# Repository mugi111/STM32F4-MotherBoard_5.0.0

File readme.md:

### 概要
1. STM32F4-MotherBoard_5.0.0  
STM32F407VGのマザーボード  
回路図，実体配線図
KiCADプロジェクト

2. RCsemiSTM32F4_Ver400
STM32F4MBライブラリ  
使用ライブラリ:SPD(Standard Peripheral Driver)  
使用言語:C

3. RCsemiSTM32F4_Ver500
STM32F4MBライブラリ  
使用ライブラリ:HAL Driver  
使用言語:C++

|STM32F4MB500|個数||
|---------|-----|-------------|
|ADC      |1    |BOXHEADER    |
|CAN      |2    |RJ45         |
|RS232C   |2    |RJ12         |
|DisitalIO|2    |BOXHEADER    |
|PushSW   |1    |DTS-6        |
|RotarySW |1    |             |
|LED      |1    |             |
|MicroSD  |1    |             |

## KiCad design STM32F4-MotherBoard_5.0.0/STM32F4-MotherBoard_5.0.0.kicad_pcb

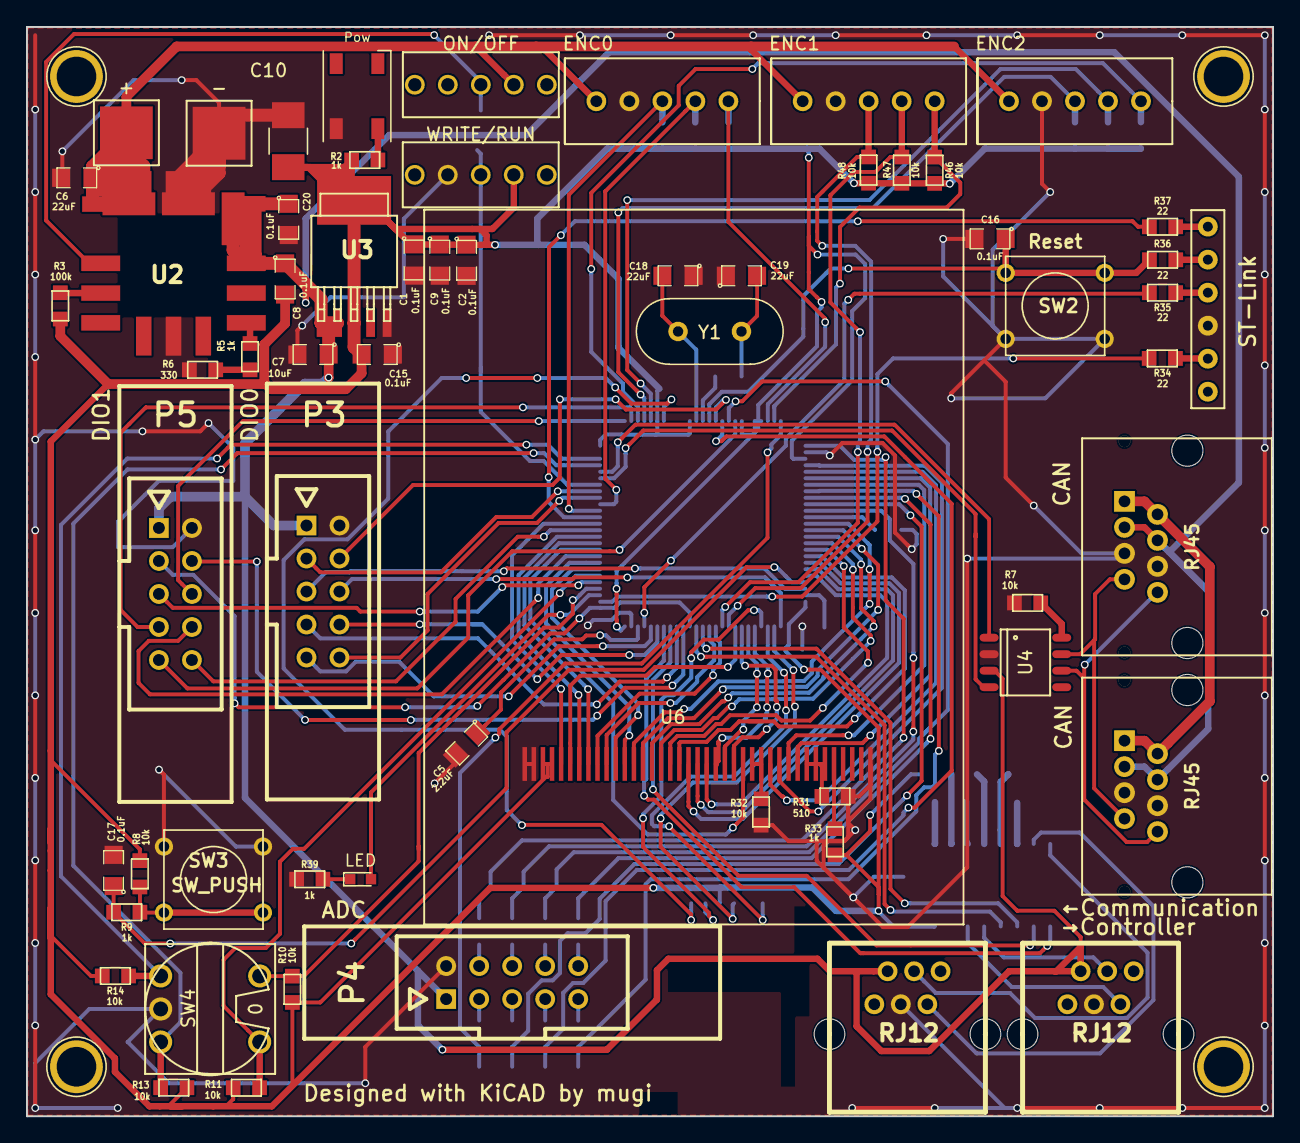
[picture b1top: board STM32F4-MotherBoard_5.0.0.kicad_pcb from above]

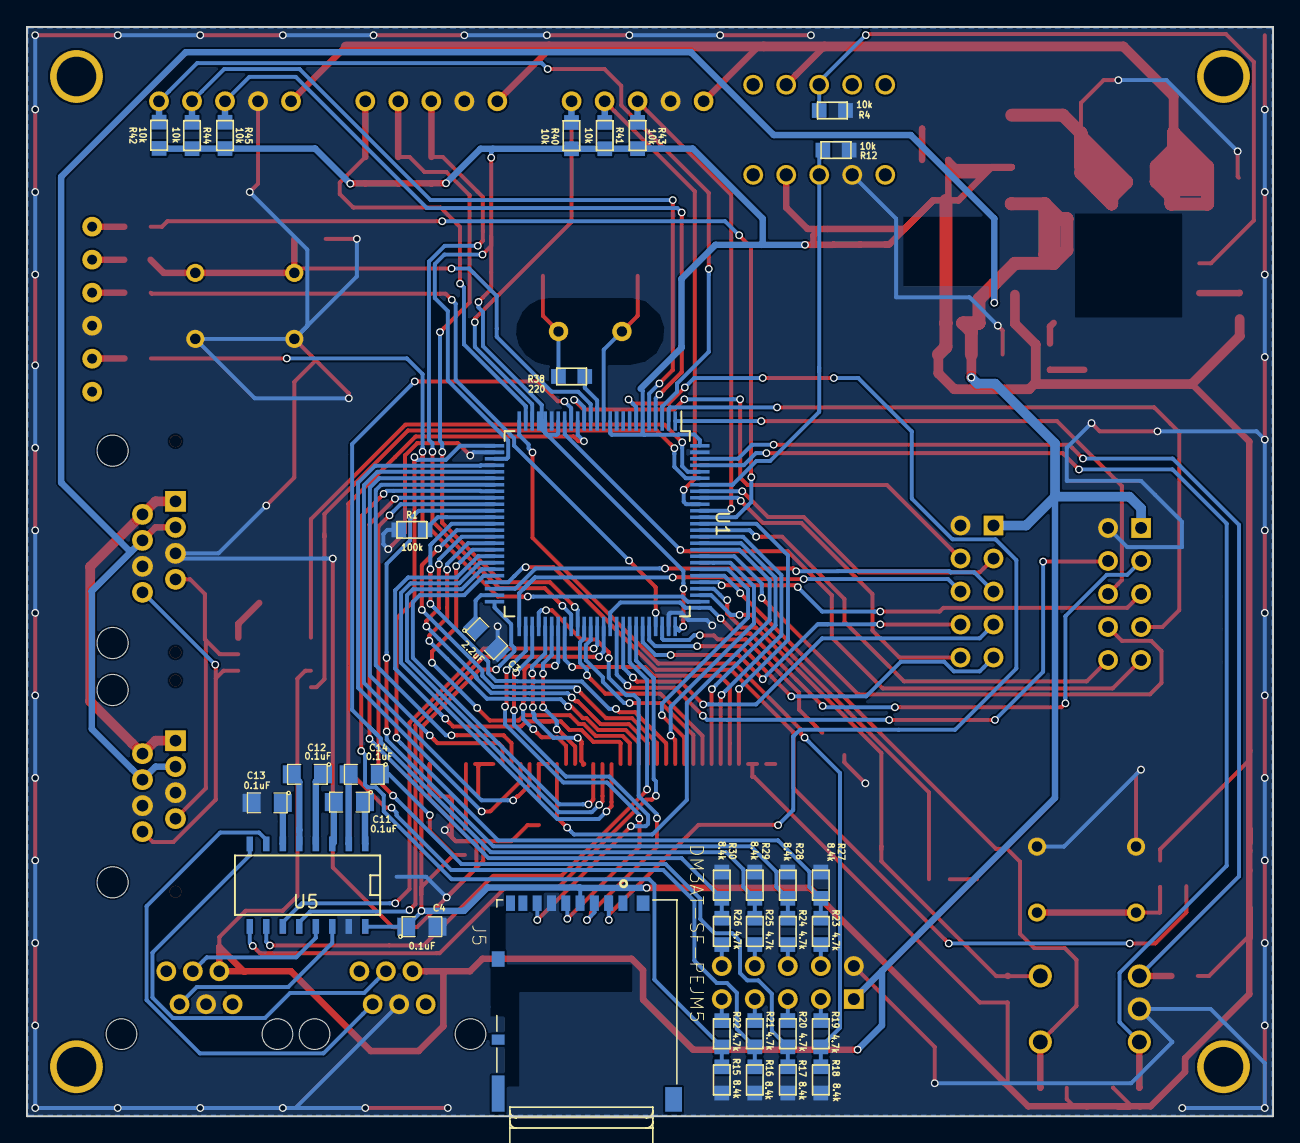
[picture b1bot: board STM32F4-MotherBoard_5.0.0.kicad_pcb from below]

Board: 2 copper layers, 95.9 x 83.8 mm, 96 parts (35 on the bottom side), 125 nets.

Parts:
+: VCC; 1Pin
-: GND; 1Pin
C1, C2, C4, C8, C9, C11, C12, C13, C14, C15, C16, C17, C20: 0.1uF; SM0805_EXP0.5mm
C3, C5: 2.2uF; SM0805_EXP0.5mm
C6, C18, C19: 22uF; SM0805_EXP0.5mm
C7: 10uF; SM0805_EXP0.5mm
C10: 47uF; C_1210_HandSoldering
CAN: RJ45; 7810-8P8C
CAN#2: RJ45; 7810-8P8C
ENC0: ENC0; XA-5
ENC1: ENC1; XA-5
ENC2: ENC2; XA-5
J5: DM3AT-SF-PEJM5; HRS_DM3AT-SF-PEJM5
LED: LED_0603
ON/OFF: ON/OFF; SW_TOGGLE_5P
P3: DIO0; RA-H101TD
P4: ADC; RA-H101TD
P5: DIO1; RA-H101TD
Pow: Power; LED_WS2812B-PLCC4
R1, R3: 100k; SM0603_EXP0.5mm
R2, R5, R9, R33, R39: 1k; SM0603_EXP0.5mm
R4, R7, R8, R10, R11, R12, R13, R14, R32, R40, R41, R42, R43, R44, R45, R46, R47, R48: 10k; SM0603_EXP0.5mm
R6: 330; SM0603_EXP0.5mm
R15, R16, R17, R18, R27, R28, R29, R30: 8.4k; SM0603_EXP0.5mm
R19, R20, R21, R22, R23, R24, R25, R26: 4.7k; SM0603_EXP0.5mm
R31: 510; SM0603_EXP0.5mm
R34, R35, R36, R37: 22; SM0603_EXP0.5mm
R38: 220; SM0603_EXP0.5mm
ST-Link: SWD; PinHeader-6
SW2: Reset; SW_PUSH
SW3: SW_PUSH
SW4: SW_ROTARY; RotarySW
U1: STM32F407VG; LQFP-100_14x14mm_Pitch0.5mm
U2: OKL-T6-W12
U3: PQ033EZ1H; PQ033EZ1HZ
U4: MCP2551-I/SN; SO-8
U5: ADM3202; SO-16-N
U6: AS021350D; ASO21350D
WRITE/RUN: WRITE/RUN; SW_TOGGLE_5P
Y1: 8MHz; Crystal_HC49-U_Vertical
←Communication: RJ12; MODULAR-JACK_6P6C
→Controller: RJ12; MODULAR-JACK_6P6C

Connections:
+3V3: C1.1, C2.1, C4.1, C8.2, C9.1, C10.2, C14.1, C15.2, J5.4, R2.1, R3.1, R8.1, R10.1, R11.1, R13.1, R14.1, R33.2, R40.1, R41.1, R42.1, R43.1, R44.1, R45.1, R46.1, R47.1, R48.1, U1.6, U1.11, U1.19, U1.21, U1.22, U1.28, U1.50, U1.75, U1.100, U3.3, U5.16, U6.3, U6.4, WRITE/RUN.2
+5V: C7.1, C8.1, C20.1, CAN.3, CAN.4, CAN#2.3, CAN#2.4, P3.1, P4.1, P5.1, U2.4, U2.5, U3.1, U3.2, U4.3, ←Communication.2, →Controller.2
+12V: +.1, C6.1, ENC0.1, ENC1.1, ENC2.1, ON/OFF.4, U2.2
+12VA: CAN.1, CAN.2, CAN#2.1, CAN#2.2
ADC0: R18.1, R19.2, U1.25
ADC1: R23.1, R27.1, U1.26
ADC2: R17.1, R20.2, U1.35
ADC3: R24.1, R28.1, U1.36
ADC4: R16.1, R21.2, U1.16
ADC5: R25.1, R29.1, U1.17
ADC6: R15.1, R22.2, U1.33
ADC7: R26.1, R30.1, U1.34
CAN_RX: U1.95, U4.4
CAN_TX: U1.96, U4.1
CS: U1.88, U6.5
DIO0_0: P3.3, U1.93
DIO0_1: P3.4, U1.15
DIO0_2: P3.5, U1.48
DIO0_3: P3.6, U1.51
DIO0_4: P3.7, U1.67
DIO0_5: P3.8, U1.70
DIO0_6: P3.9, U1.71
DIO0_7: P3.10, U1.92
DIO1_0: P5.3, U1.65
DIO1_1: P5.4, U1.66
DIO1_2: P5.5, U1.79
DIO1_3: P5.6, U1.1
DIO1_4: P5.7, U1.2
DIO1_5: P5.8, U1.83
DIO1_6: P5.9, U1.18
DIO1_7: P5.10, U1.87
ENC0_A: ENC0.3, R43.2, U1.90
ENC0_B: ENC0.4, R41.2, U1.91
ENC0_Z: ENC0.5, R40.2, U1.23
ENC1_A: ENC1.3, R48.2, U1.59
ENC1_B: ENC1.4, R47.2, U1.60
ENC1_Z: ENC1.5, R46.2, U1.24
ENC2_A: ENC2.3, R45.2, U1.4
ENC2_B: ENC2.4, R44.2, U1.5
ENC2_Z: ENC2.5, R42.2, U1.3
FSMC_D0: U1.61, U6.9
FSMC_D1: U1.62, U6.10
FSMC_D2: U1.81, U6.11
FSMC_D3: U1.82, U6.12
FSMC_D4: U1.38, U6.13
FSMC_D5: U1.39, U6.14
FSMC_D6: U1.40, U6.15
FSMC_D7: U1.41, U6.16
FSMC_D8: U1.42, U6.17
FSMC_D9: U1.43, U6.18
FSMC_D10: U1.44, U6.19
FSMC_D11: U1.45, U6.20
FSMC_D12: U1.46, U6.21
FSMC_D13: U1.55, U6.22
FSMC_D14: U1.56, U6.23
FSMC_D15: U1.57, U6.24
GND: -.1, C1.2, C2.2, C3.2, C4.2, C5.2, C6.2, C7.2, C9.2, C10.1, C13.2, C15.1, C16.2, C17.2, C18.1, C19.1, C20.2, CAN.5, CAN.6, CAN#2.5, CAN#2.6, ENC0.2, ENC1.2, ENC2.2, J5.6, P3.2, P4.2, P5.2, Pow.1, R1.2, R4.2, R6.2, R7.2, R12.2, R15.2, R16.2, R17.2, R18.2, R27.2, R28.2, R29.2, R30.2, R31.2, R32.2, R39.2, ST-Link.3, SW2.2, SW3.1, SW4.4, U1.10, U1.20, U1.27, U1.74, U1.99, U2.3, U2.7, U3.5, U4.2, U5.15, U6.1, U6.2, U6.39, WRITE/RUN.4, ←Communication.3, →Controller.3
LED: LED.2, U1.77
NRST: C16.1, R36.1, SW2.1, U1.14
unnamed: C3.1, U1.49
unnamed: C5.1, U1.73
unnamed: C11.1, U5.1
unnamed: C11.2, U5.3
unnamed: C12.1, U5.4
unnamed: C12.2, U5.5
unnamed: C13.1, U5.6
unnamed: C14.2, U5.2
unnamed: C19.2, R38.1, Y1.2
unnamed: Pow.2, R2.2
unnamed: LED.1, R39.1
unnamed: CAN.7, CAN#2.7, U4.7
unnamed: CAN.8, CAN#2.8, U4.6
unnamed: U5.13, →Controller.4
unnamed: U5.14, →Controller.5
unnamed: U5.8, ←Communication.4
unnamed: U5.7, ←Communication.5
unnamed: P4.3, R19.1
unnamed: P4.4, R23.2
unnamed: P4.5, R20.1
unnamed: P4.6, R24.2
unnamed: P4.7, R21.1
unnamed: P4.8, R25.2
unnamed: P4.9, R22.1
unnamed: P4.10, R26.2
unnamed: R34.2, ST-Link.2
unnamed: R35.2, ST-Link.4
unnamed: R36.2, ST-Link.5
unnamed: R37.2, ST-Link.6
unnamed: R1.1, U1.37
unnamed: R3.2, U2.10
unnamed: ON/OFF.3, R4.1, U2.1
unnamed: R5.1, U2.6
unnamed: R5.2, R6.1
unnamed: R7.1, U4.8
unnamed: R8.2, R9.2, SW3.2
unnamed: R31.1, U6.32, U6.33, U6.34
unnamed: R32.1, U6.26, U6.27
unnamed: R33.1, U6.35
OSC_IN: C18.2, U1.12, Y1.1
OSC_OUT: R38.2, U1.13
PushSW: C17.1, R9.1, U1.47
RD: U1.85, U6.8
RS: U1.58, U6.6
RS-232(Controller)_RX: U1.64, U5.12
RS-232(Controller)_TX: U1.63, U5.11
RS-232(PC)_RX: U1.69, U5.9
RS-232(PC)_TX: U1.68, U5.10
RST: U1.84, U6.25
RotarySW0: R10.2, SW4.1, U1.78
RotarySW1: R11.2, SW4.2, U1.80
RotarySW2: R13.2, SW4.3, U1.97
RotarySW3: R14.2, SW4.5, U1.98
SPI_CS: J5.2, U1.7
SPI_MISO: J5.7, U1.53
SPI_MOSI: J5.3, U1.54
SPI_SCK: J5.5, U1.52
SWCLK: R34.1, U1.76
SWDIO: R35.1, U1.72
SWO: R37.1, U1.89
WR: U1.86, U6.7
Write: R12.1, U1.94, WRITE/RUN.3
XL: U1.29, U6.29
XR: U1.31, U6.31
YB: U1.30, U6.28
YT: U1.32, U6.30

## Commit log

2017-02-08 init
2017-02-08 シート作成
2017-02-08 readme更新
2017-02-08 だいたい確定
2017-02-08 シート追加
2017-02-11 機能名の変更
2017-02-11 ラベルの作成
2017-02-11 rename
2017-02-11 add lib
2017-02-11 DIO-ADC
2017-02-11 Display
2017-02-11 ST-Link
2017-02-11 power
2017-02-11 RS-232
2017-02-11 add LED
2017-02-11 add run write
2017-02-11 ラベル方向設定
2017-02-11 大枠の電源
2017-02-14 SDとCANの追加とラベルミス修正
2017-02-16 回路図終わり
2017-02-16 部品名変更
2017-02-16 CSピン追加
2017-02-19 関連付けできたの
2017-02-19 部品配置
2017-02-28 部品配置終わり
2017-03-07 部品配置再考終わり
2017-04-20 add c++Ver Proj
2017-04-20 add timerClass
2017-04-24 change timer.cpp
2017-04-25 add motor
2017-04-25 change func name
2017-04-25 add xprintf
2017-04-25 add can class
2017-04-25 add can.cpp
2017-04-26 add Garver
2017-04-26 replace project
2017-04-27 なんか変わった
2017-04-27 何が変わったかわからない
2017-04-27 コンストラクタの追加
2017-04-27 コンストラクタの追加したりしなかったり
2017-05-03 自由に使えるやつのあれの外枠を追加
2017-05-03 インデント直した
2017-05-03 仕様変わりすぎてたからちょっと保留
2017-05-03 SPDからHALへの変更でIRQHandlerを消した
2017-05-03 motor driveの中身追加した
2017-05-16 digitalIOピン変更
2017-05-16 LEDとPushSWの変更に伴う引数の削除
2017-05-17 MB関数変更(LED)
2017-05-17 fatfs追加
2017-05-17 example追加main削除
2017-05-17 example中身
2017-05-17 readme書き加え
2017-05-17 表書き換え
2017-05-17 readme書き換え
2017-05-17 includeかわった
2017-05-17 なんかわからない
2017-05-20 rs485 .c .h example remove
2017-05-20 うごくといいな
2017-05-20 exampleヘッダー書き換え CAN example一時削除
2017-05-20 exampleヘッダー対応
2017-05-20 exampleヘッダー書き換え
2017-05-20 CAN_Motor_Drive書いたけど動く気がしない
2017-05-20 アドレスに関して書き換え
2017-05-20 引数type追加
2017-05-20 適当にDIOも
2017-06-02 スペルミス修正
2017-06-03 ほとんどの機能試せた
2017-06-03 MDの引数を構造体に
2017-06-19 初期化成功するようになった
2017-06-23 loopback成功
2017-06-29 usart2IRQn -> usart6IRQn
2017-06-29 readme修正
2017-06-29 SendFrameの関数名，引数名の変更とテスト用loopbackのプログラム削除
2017-06-29 CAN関連の関数名引数名の変更とFrameMode(REMOTE, DATA)を選択できるように
2017-06-29 CAN非常停止関数の引数を列挙型に
2017-06-29 CAN:関数が複雑になるためFilterConfig関数の削除と仮想的なMasterとしてのフィルター設定をInit関数内でするように変更
2017-06-29 DIOの状態を要求する関数を書いたがデータの受取に関して考える必要があるためコメントアウトそれに伴ったOutput関数の変更
2017-07-10 coide to sw4stm32
2017-07-10 change sample
